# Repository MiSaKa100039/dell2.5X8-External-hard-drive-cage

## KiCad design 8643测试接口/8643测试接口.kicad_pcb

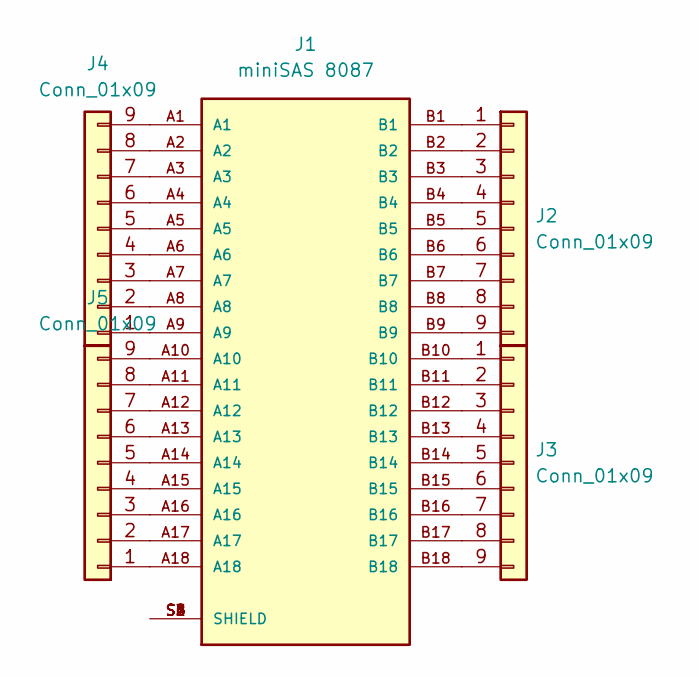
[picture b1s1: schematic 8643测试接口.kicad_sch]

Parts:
J1: miniSAS 8087
J2, J3, J4, J5: Conn_01x09; PinSocket_1x09_P2.00mm_Vertical_test; Part Number 1-0901FBV0T

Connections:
GND: J1.S1 (SHIELD), J1.S2 (SHIELD), J1.S3 (SHIELD), J1.S4 (SHIELD), J1.S5 (SHIELD), J1.S6 (SHIELD)
unnamed: J1.B1, J2.1
unnamed: J1.B2, J2.2
unnamed: J1.B3, J2.3
unnamed: J1.B4, J2.4
unnamed: J1.B5, J2.5
unnamed: J1.B6, J2.6
unnamed: J1.B7, J2.7
unnamed: J1.B8, J2.8
unnamed: J1.B9, J2.9
unnamed: J1.B10, J3.1
unnamed: J1.B11, J3.2
unnamed: J1.B12, J3.3
unnamed: J1.B13, J3.4
unnamed: J1.B14, J3.5
unnamed: J1.B15, J3.6
unnamed: J1.B16, J3.7
unnamed: J1.B17, J3.8
unnamed: J1.B18, J3.9
unnamed: J1.A9, J4.1
unnamed: J1.A8, J4.2
unnamed: J1.A7, J4.3
unnamed: J1.A6, J4.4
unnamed: J1.A5, J4.5
unnamed: J1.A4, J4.6
unnamed: J1.A3, J4.7
unnamed: J1.A2, J4.8
unnamed: J1.A1, J4.9
unnamed: J1.A18, J5.1
unnamed: J1.A17, J5.2
unnamed: J1.A16, J5.3
unnamed: J1.A15, J5.4
unnamed: J1.A14, J5.5
unnamed: J1.A13, J5.6
unnamed: J1.A12, J5.7
unnamed: J1.A11, J5.8
unnamed: J1.A10, J5.9

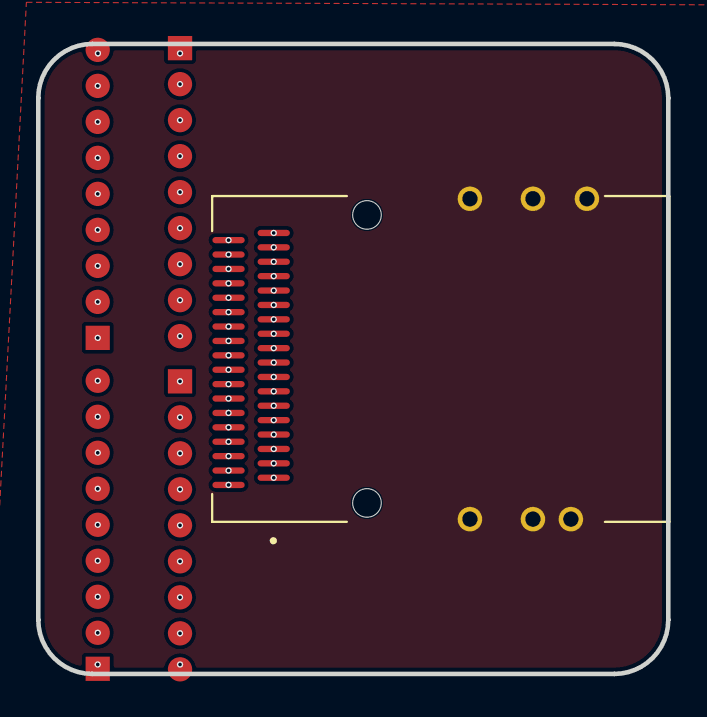
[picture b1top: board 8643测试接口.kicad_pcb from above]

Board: 4 copper layers, 35.0 x 35.0 mm, 5 parts (0 on the bottom side), 37 nets.

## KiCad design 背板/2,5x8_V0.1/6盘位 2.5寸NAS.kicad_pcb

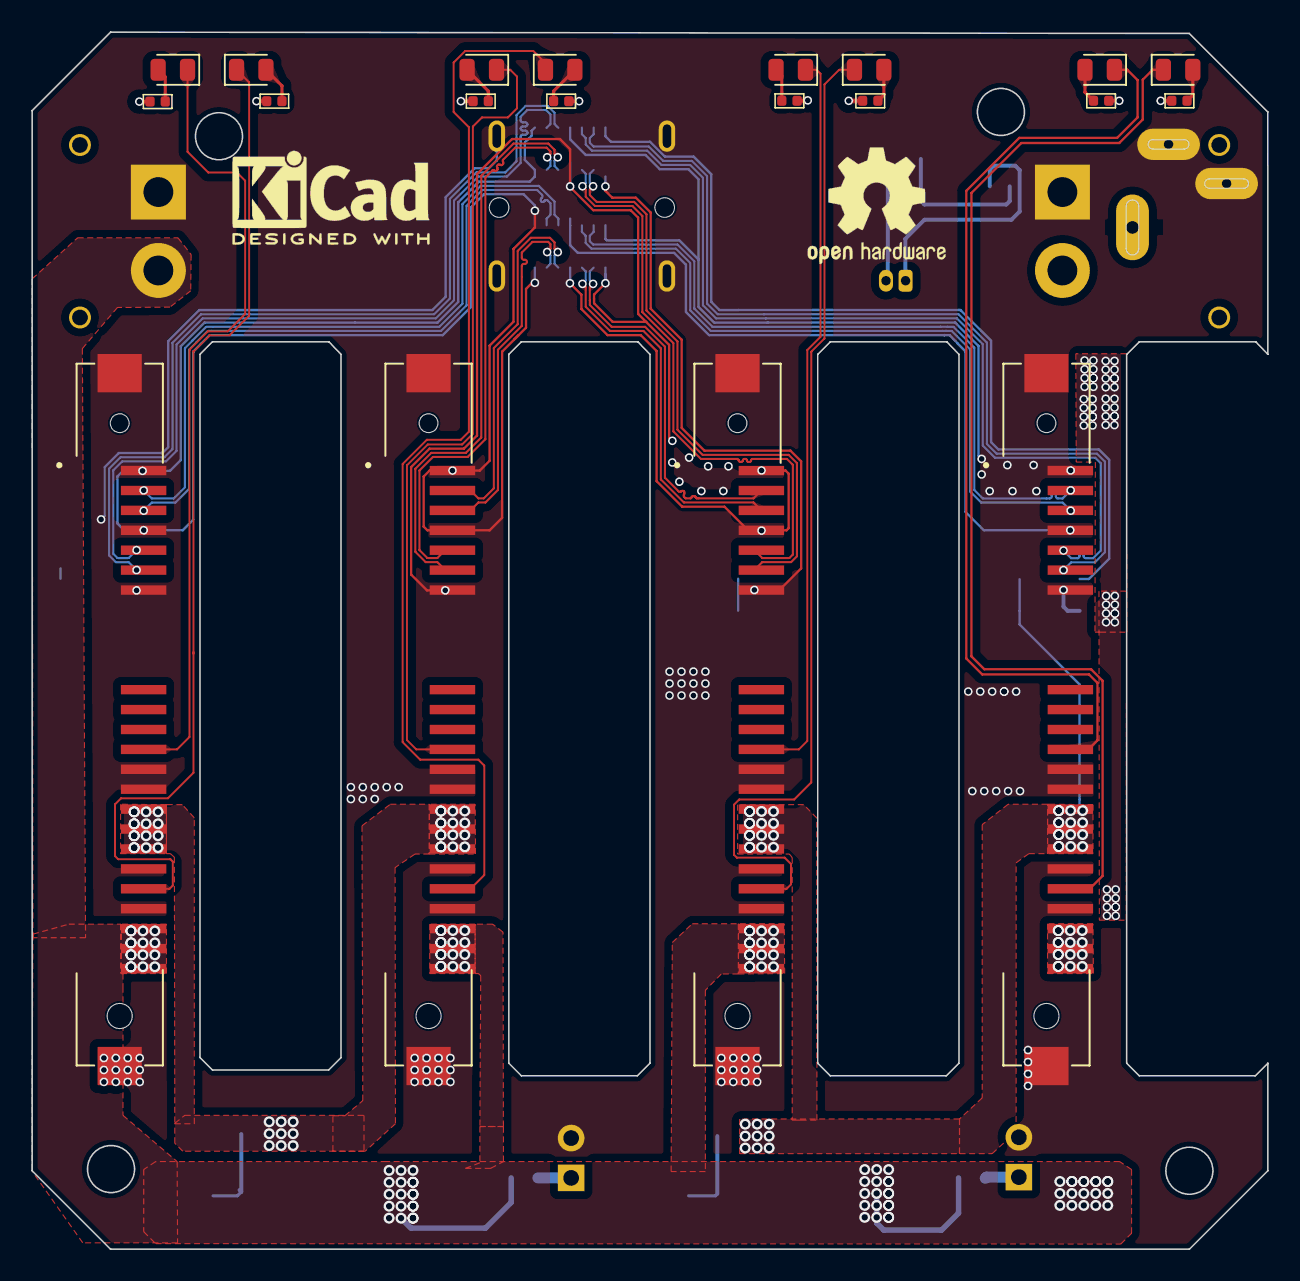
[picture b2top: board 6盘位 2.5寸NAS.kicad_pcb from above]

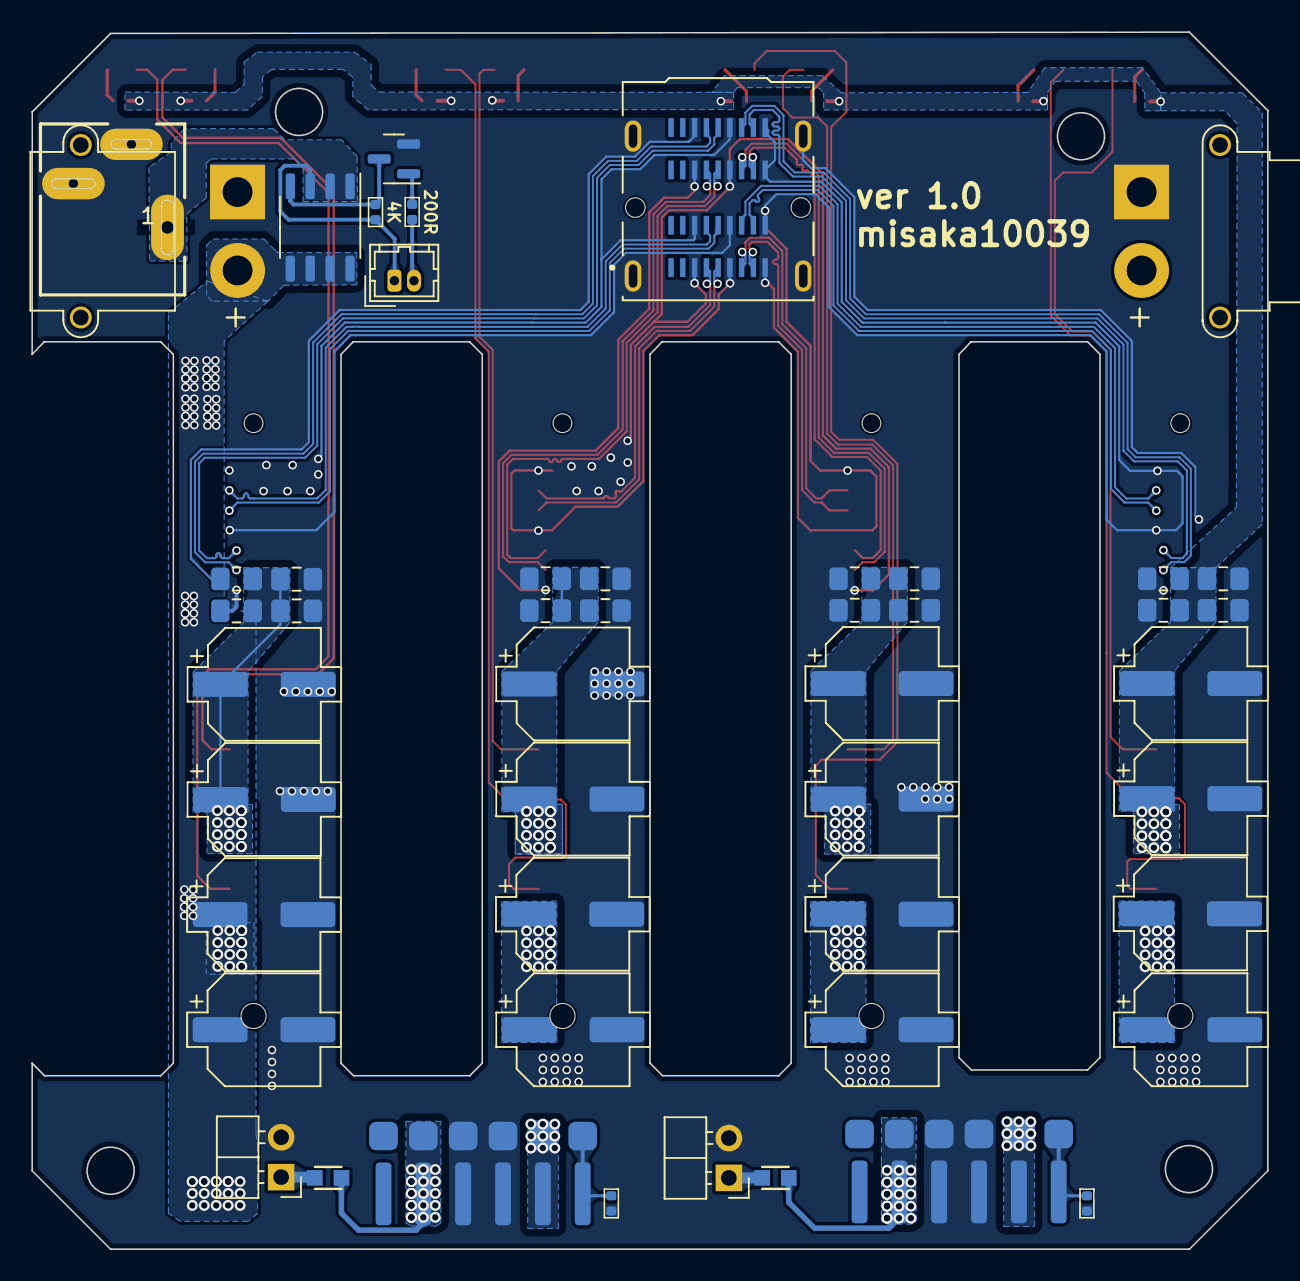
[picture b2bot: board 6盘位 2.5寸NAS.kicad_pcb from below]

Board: 2 copper layers, 78.8 x 77.6 mm, 66 parts (46 on the bottom side), 41 nets.

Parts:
4K: 4k; R_0402
200R: 200R; R_0402
C1, C2, C3, C4, C5, C6, C7, C8: 270uF; CP_Elec_6.3x5.4
C10, C12, C14, C16: 220uF; C_0805_2012Metric_Pad1.18x1.45mm_HandSolder
C18, C20, C22, C24: 1uF; C_0805_2012Metric_Pad1.18x1.45mm_HandSolder
C26, C28, C30, C32: 100nF; C_0805_2012Metric_Pad1.18x1.45mm_HandSolder
C33, C34, C35, C36, C37, C38, C39, C40: 22uF; CP_Elec_6.3x5.3
C42, C44, C46, C48: 100uF; C_0805_2012Metric_Pad1.18x1.45mm_HandSolder
D1, D2, D3, D4, D5, D6, D7, D8: LED; LED_0805_2012Metric
J1, J2, J4, J6: SATA硬盘插头; SATA 29pin smd
J3: G40H2132212HR; AMPHENOL_G40H2132212HR
J7: XT30PW-M; AMASS_XT30PW-F_1x02_P2.50mm_Horizontal
J8: XT30PW-M; AMASS_XT30PW-M_1x02_P2.50mm_Horizontal
J9: fan1; PinHeader_1x02_P2.54mm_Horizontal
J10: fan2; PinHeader_1x02_P2.54mm_Horizontal
J11: 694108402002; DC socket 5.5mm
R1, R4: 100R 1%; R_0402
R2, R5, R6, R7, R8, R9: 2k; R_0402
R5#2, R5#3: 2k; R_0603
Re: 2k; R_0402
Re#2: 2k; R_0402
U1, U2: ZXDN10

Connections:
1A+: J1.S6, J3.D4
1A-: J1.S5, J3.D5
1B+: J1.S2, J3.B4
1B-: J1.S3, J3.B5
2A+: J2.S6, J3.C4
2A-: J2.S5, J3.C5
2B+: J2.S2, J3.A4
2B-: J2.S3, J3.A5
3A+: J3.D7, J4.S6
3A-: J3.D8, J4.S5
3B+: J3.B7, J4.S2
3B-: J3.B8, J4.S3
4A+: J3.C7, J6.S6
4A-: J3.C8, J6.S5
4B+: J3.A7, J6.S2
4B-: J3.A8, J6.S3
+12V: C1.1, C3.1, C5.1, C7.1, C33.1, C35.1, C37.1, C39.1, J1.P13, J1.P14, J1.P15, J2.P13, J2.P14, J2.P15, J4.P13, J4.P14, J4.P15, J6.P13, J6.P14, J6.P15, J7.2, J8.2, R5#2.2, R5#3.2, U1.2 (VIN), U2.2 (VIN)
/DAS1: D2.1 (K), J1.P11
/DAS2: D3.1 (K), J2.P11
/DAS3: D5.1 (K), J4.P11
/DAS4: D7.1 (K), J6.P11
/HOT1: D1.1 (K), J1.P4
/HOT2: D4.1 (K), J2.P4
/HOT3: D6.1 (K), J4.P4
/HOT4: D8.1 (K), J6.P4
DCIN: 4K.2, J11.1
GND: C1.2, C2.2, C3.2, C4.2, C5.2, C6.2, C7.2, C8.2, C10.1, C12.1, C14.1, C16.1, C18.1, C20.1, C22.1, C24.1, C26.1, C28.1, C30.1, C32.1, C33.2, C34.2, C35.2, C36.2, C37.2, C38.2, C39.2, C40.2, C42.1, C44.1, C46.1, C48.1, J1.P5, J1.P6, J1.P10, J1.P12, J1.S1, J1.S4, J1.S7, J1.SH1 (SHIELD), J1.SH2 (SHIELD), J2.P5, J2.P6, J2.P10, J2.P12, J2.S1, J2.S4, J2.S7, J2.SH1 (SHIELD), J2.SH2 (SHIELD), J3.A3, J3.A6, J3.A9, J3.B3, J3.B6, J3.B9, J3.C3, J3.C6, J3.C9, J3.D3, J3.D6, J3.D9, J3.SH1, J3.SH2, J3.SH3, J3.SH4, J4.P5, J4.P6, J4.P10, J4.P12, J4.S1, J4.S4, J4.S7, J4.SH1 (SHIELD), J4.SH2 (SHIELD), J6.P5, J6.P6, J6.P10, J6.P12, J6.S1, J6.S4, J6.S7, J6.SH1 (SHIELD), J6.SH2 (SHIELD), J7.1 (N), J8.1 (N), J9.2, J10.2, J11.2, J11.3, R1.2, R4.2, U1.3 (GND), U1.4 (GND), U2.3 (GND), U2.4 (GND)
unnamed: D1.2 (A), R2.2
unnamed: D2.2 (A), Re.2
unnamed: D3.2 (A), R5.2
unnamed: D4.2 (A), R6.2
unnamed: D5.2 (A), R7.2
unnamed: D6.2 (A), R8.2
unnamed: D7.2 (A), R9.2
unnamed: D8.2 (A), Re#2.2
unnamed: R1.1, U1.6 (ADJ)
unnamed: R4.1, U2.6 (ADJ)
fan1: J9.1, R5#2.1
fan2: J10.1, R5#3.1
vout1: C2.1, C4.1, C10.2, C12.2, C18.2, C20.2, C26.2, C28.2, C34.1, C36.1, C42.2, C44.2, J4.P7, J4.P8, J4.P9, J6.P7, J6.P8, J6.P9, R2.1, R5.1, R6.1, R7.1, R8.1, R9.1, Re.1, Re#2.1, U1.5 (VOUT)
vout2: C6.1, C8.1, C14.2, C16.2, C22.2, C24.2, C30.2, C32.2, C38.1, C40.1, C46.2, C48.2, J1.P7, J1.P8, J1.P9, J2.P7, J2.P8, J2.P9, U2.5 (VOUT)

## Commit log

2024-04-11 ver1.0
